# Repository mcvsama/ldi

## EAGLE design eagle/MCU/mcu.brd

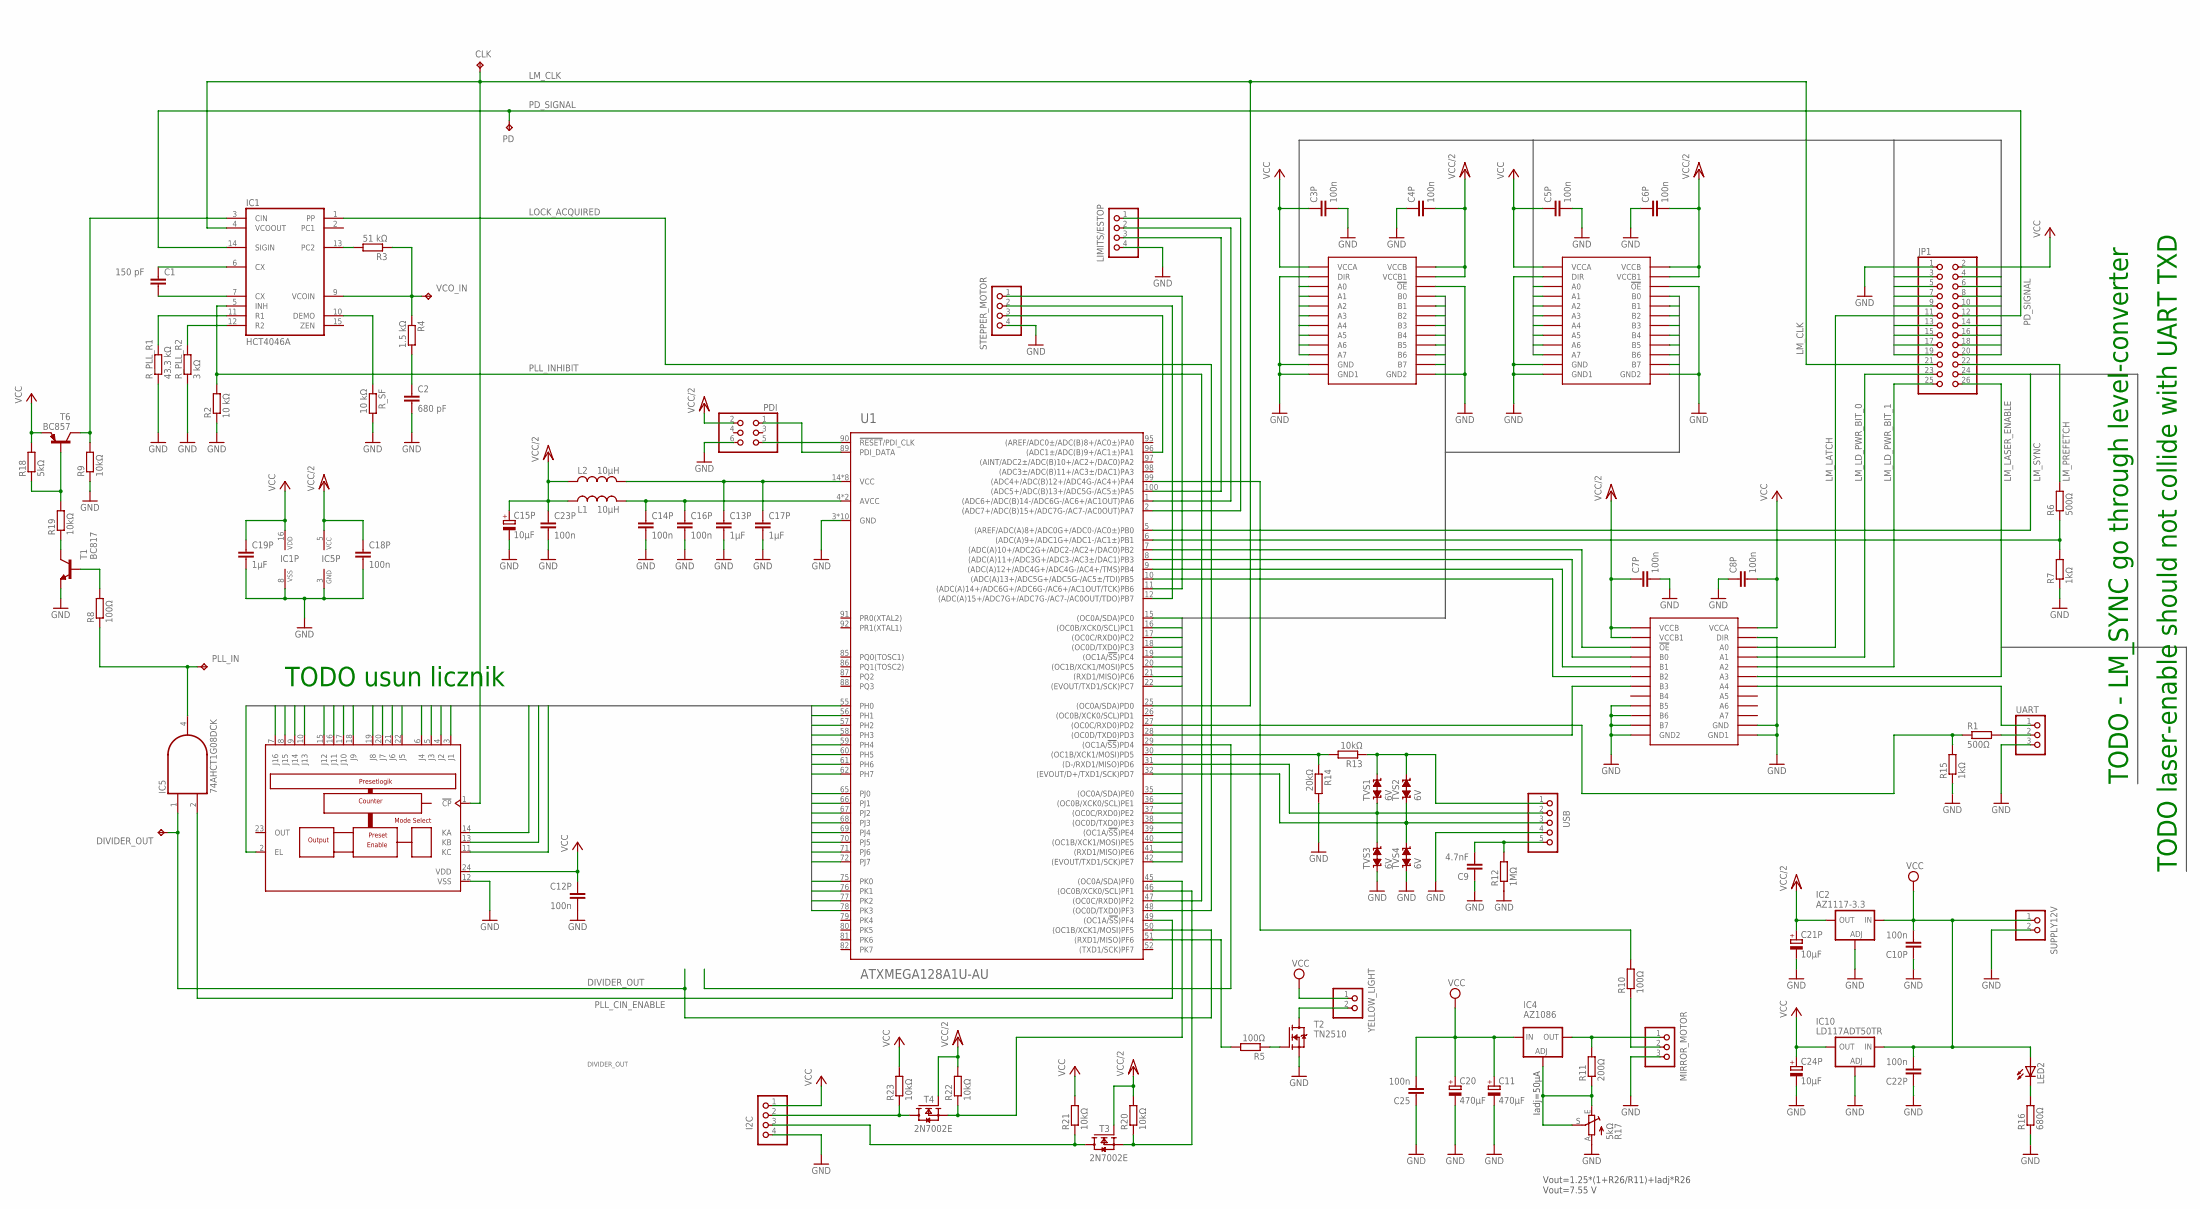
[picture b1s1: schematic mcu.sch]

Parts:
C1: 150 pF; C1206
C2: 680 pF; C1206
C3P, C4P, C5P, C6P, C7P, C8P: 100n; C0603
C9: 4.7nF; C1206
C10P, C12P, C14P, C16P, C18P, C22P, C23P, C25: 100n; C1206
C11, C20: 470µF; 153CLV-0807
C13P, C17P, C19P: 1µF; C1206
C15P, C21P, C24P: 10µF; A/3216-18R
CLK: TPB1,27; B1,27
DIVIDER_OUT: TPB1,27; B1,27
I2C: PINHD-1X4; 1X04
IC1: HCT4046A; SO16
IC2: AZ1117-3.3; DPACK
IC3: 4059D; SO24W
IC4: AZ1086; D2PACK
IC5: 74AHCT1G08DCK; SC70-5
IC7, IC8, IC9: 74LVX4245TSSOP24W; TSSOP-24-W
IC10: LD117ADT50TR; DPACK
JP1: PINHD-2X13; 2X13
L1, L2: 10µH; L1812
LED2: LEDCHIPLED_0805; CHIPLED_0805
LIMITS/ESTOP: PINHD-1X4; 1X04
MIRROR_MOTOR: PINHD-1X3; 1X03
PD: TPB1,27; B1,27
PDI: PINHD-2X3; 2X03
PLL_IN: TPB1,27; B1,27
R1, R6: 500Ω; R0603
R2: 10 kΩ; R0603
R3: 51 kΩ; R0603
R4: 1.5 kΩ; R0603
R5, R8, R10: 100Ω; R0603
R7, R15: 1kΩ; R0603
R9, R13, R19, R20, R21, R22, R23: 10kΩ; R0603
R11: 200Ω; R1206
R12: 1MΩ; R0603
R14: 20kΩ; R0603
R16: 680Ω; R0603
R17: 5kΩ; B64Y
R18: 5kΩ; R0603
R_PLL_R1: 43.3 kΩ; R0603
R_PLL_R2: 3 kΩ; R0603
R_SF: 10 kΩ; R0603
STEPPER_MOTOR: PINHD-1X4; 1X04
SUPPLY12V: PINHD-1X2; 1X02
T1: BC817; SOT23-BEC
T2: TN2510; SOT89
T3, T4: 2N7002E; SOT23
T6: BC857; SOT23-BEC
TVS1, TVS2, TVS3, TVS4: 6V; TVS0805
U1: ATXMEGA128A1U-AU; TQFP-100A-100
UART: PINHD-1X3; 1X03
USB: PINHD-1X5; 1X05
VCO_IN: TPB1,27; B1,27
YELLOW_LIGHT: PINHD-1X2; 1X02

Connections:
CTR0_KA: IC3.14 (KA), U1.75 (PK0)
CTR0_KB: IC3.13 (KB), U1.76 (PK1)
CTR0_KC: IC3.11 (KC), U1.77 (PK2)
CTR0_LE: IC3.2 (EL), U1.78 (PK3)
CTR0_PROG0: IC3.3 (J1), U1.55 (PH0)
CTR0_PROG1: IC3.4 (J2), U1.56 (PH1)
CTR0_PROG2: IC3.5 (J3), U1.57 (PH2)
CTR0_PROG3: IC3.6 (J4), U1.58 (PH3)
CTR0_PROG4: IC3.22 (J5), U1.59 (PH4)
CTR0_PROG5: IC3.21 (J6), U1.60 (PH5)
CTR0_PROG6: IC3.20 (J7), U1.61 (PH6)
CTR0_PROG7: IC3.19 (J8), U1.62 (PH7)
CTR0_PROG8: IC3.18 (J9), U1.65 (PJ0)
CTR0_PROG9: IC3.17 (J10), U1.66 (PJ1)
CTR0_PROG10: IC3.16 (J11), U1.67 (PJ2)
CTR0_PROG11: IC3.15 (J12), U1.68 (PJ3)
CTR0_PROG12: IC3.10 (J13), U1.69 (PJ4)
CTR0_PROG13: IC3.9 (J14), U1.70 (PJ5)
CTR0_PROG14: IC3.8 (J15), U1.71 (PJ6)
CTR0_PROG15: IC3.7 (J16), U1.72 (PJ7)
DIVIDER_OUT: DIVIDER_OUT.TP, IC5.1 (I0), U1.50 ((OC1B/XCK1/MOSI)PF5)
GND: C2.2, C3P.2, C4P.1, C5P.2, C6P.1, C7P.2, C8P.1, C9.1, C10P.1, C11.-, C12P.1, C13P.2, C14P.2, C15P.-, C16P.2, C17P.2, C18P.2, C19P.2, C20.-, C21P.-, C22P.1, C23P.2, C24P.-, C25.1, I2C.4, IC1.8 (VSS), IC2.1 (ADJ), IC3.12 (VSS), IC5.3 (GND), IC7.2 (DIR), IC7.11 (GND), IC7.12 (GND1), IC7.13 (GND2), IC7.22 (!OE), IC8.2 (DIR), IC8.11 (GND), IC8.12 (GND1), IC8.13 (GND2), IC8.22 (!OE), IC9.2 (DIR), IC9.11 (GND), IC9.12 (GND1), IC9.13 (GND2), IC9.14 (B7), IC9.15 (B6), IC9.16 (B5), IC10.1 (ADJ), JP1.1, LIMITS/ESTOP.4, MIRROR_MOTOR.3, PDI.6, R2.1, R7.1, R9.1, R12.1, R14.2, R15.1, R16.1, R17.A, R_PLL_R1.1, R_PLL_R2.1, R_SF.2, STEPPER_MOTOR.4, SUPPLY12V.2, T1.E, T2.3 (S), TVS3.1, TVS4.1, U1.3 (GND), U1.13 (GND), U1.23 (GND), U1.33 (GND), U1.43 (GND), U1.53 (GND), U1.63 (GND), U1.73 (GND), U1.84 (GND), U1.93 (GND), UART.3, USB.4
I2C_SDA_3V2: R20.1, T3.2 (S), U1.46 ((OC0B/XCK0/SCL)PF1)
I2C_SDA_3V4: R22.1, T4.2 (S), U1.45 ((OC0A/SDA)PF0)
I2C_SDA_5V2: I2C.3, R21.1, T3.3 (D)
I2C_SDA_5V3: I2C.2, R23.1, T4.3 (D)
LM_CLK: CLK.TP, IC1.4 (VCOOUT), IC3.1 (!CP), JP1.21, U1.25 ((OC0A/SDA)PD0)
LM_DATA_3V3_0: IC7.21 (B0), U1.35 ((OC0A/SDA)PE0)
LM_DATA_3V3_1: IC7.20 (B1), U1.36 ((OC0B/XCK0/SCL)PE1)
LM_DATA_3V3_2: IC7.19 (B2), U1.37 ((OC0C/RXD0)PE2)
LM_DATA_3V3_3: IC7.18 (B3), U1.38 ((OC0D/TXD0)PE3)
LM_DATA_3V3_4: IC7.17 (B4), U1.39 ((OC1A/!SS!)PE4)
LM_DATA_3V3_5: IC7.16 (B5), U1.40 ((OC1B/XCK1/MOSI)PE5)
LM_DATA_3V3_6: IC7.15 (B6), U1.41 ((RXD1/MISO)PE6)
LM_DATA_3V3_7: IC7.14 (B7), U1.42 ((EVOUT/TXD1/SCK)PE7)
LM_DATA_3V3_8: IC8.21 (B0), U1.15 ((OC0A/SDA)PC0)
LM_DATA_3V3_9: IC8.20 (B1), U1.16 ((OC0B/XCK0/SCL)PC1)
LM_DATA_3V3_10: IC8.19 (B2), U1.17 ((OC0C/RXD0)PC2)
LM_DATA_3V3_11: IC8.18 (B3), U1.18 ((OC0D/TXD0)PC3)
LM_DATA_3V3_12: IC8.17 (B4), U1.19 ((OC1A/!SS!)PC4)
LM_DATA_3V3_13: IC8.16 (B5), U1.20 ((OC1B/XCK1/MOSI)PC5)
LM_DATA_3V3_14: IC8.15 (B6), U1.21 ((RXD1/MISO)PC6)
LM_DATA_3V3_15: IC8.14 (B7), U1.22 ((EVOUT/TXD1/SCK)PC7)
LM_DATA_5V0: IC7.10 (A7), JP1.3
LM_DATA_5V1: IC7.9 (A6), JP1.4
LM_DATA_5V2: IC7.8 (A5), JP1.5
LM_DATA_5V3: IC7.7 (A4), JP1.6
LM_DATA_5V4: IC7.6 (A3), JP1.7
LM_DATA_5V5: IC7.5 (A2), JP1.8
LM_DATA_5V6: IC7.4 (A1), JP1.9
LM_DATA_5V7: IC7.3 (A0), JP1.10
LM_DATA_5V8: IC8.10 (A7), JP1.13
LM_DATA_5V9: IC8.9 (A6), JP1.14
LM_DATA_5V10: IC8.8 (A5), JP1.15
LM_DATA_5V11: IC8.7 (A4), JP1.16
LM_DATA_5V12: IC8.6 (A3), JP1.17
LM_DATA_5V13: IC8.5 (A2), JP1.18
LM_DATA_5V14: IC8.4 (A1), JP1.19
LM_DATA_5V15: IC8.3 (A0), JP1.20
LM_LASER_ENABLE: IC9.6 (A3), JP1.26
LM_LATCH: IC9.3 (A0), JP1.11
LM_LD_PWR_BIT_0: IC9.4 (A1), JP1.23
LM_LD_PWR_BIT_1: IC9.5 (A2), JP1.25
LM_PREFETCH: JP1.22, R6.2
LM_SYNC: JP1.24
LOCK_ACQUIRED: IC1.1 (PP), U1.48 ((OC0D/TXD0)PF3)
unnamed: R6.1, R7.2, U1.6 ((ADC(A)9+/ADC1G+/ADC1-/AC1±)PB1)
unnamed: R18.1, R19.2, T6.B
unnamed: LIMITS/ESTOP.3, U1.100 ((ADC5+/ADC(B)13+/ADC5G-/AC5±)PA5)
unnamed: R5.2, U1.51 ((RXD1/MISO)PF6)
unnamed: PDI.1, U1.89 (PDI_DATA)
unnamed: C1.1, IC1.6 (CX)
unnamed: IC9.22 (!OE), U1.7 ((ADC(A)10+/ADC2G+/ADC2-/AC2+/DAC0)PB2)
unnamed: C1.2, IC1.7 (CX)
unnamed: IC1.13 (PC2), R3.2
unnamed: IC1.9 (VCOIN), R3.1, R4.1, VCO_IN.TP
unnamed: C2.1, R4.2
unnamed: IC1.10 (DEMO), R_SF.1
unnamed: IC1.11 (R1), R_PLL_R1.2
unnamed: IC1.12 (R2), R_PLL_R2.2
unnamed: IC9.21 (B0), U1.8 ((ADC(A)11+/ADC3G+/ADC3-/AC3±/DAC1)PB3)
unnamed: IC9.20 (B1), U1.9 ((ADC(A)12+/ADC4G+/ADC4G-/AC4+/TMS)PB4)
unnamed: IC9.19 (B2), U1.10 ((ADC(A)13+/ADC5G+/ADC5G-/AC5±/TDI)PB5)
unnamed: IC4.1 (ADJ), R11.1, R17.E, R17.S
unnamed: IC4.2 (OUT), MIRROR_MOTOR.1, R11.2
unnamed: R10.2, U1.99 ((ADC4+/ADC(B)12+/ADC4G-/AC4+)PA4)
unnamed: T2.2 (D), T2.2@1 (D), YELLOW_LIGHT.2
unnamed: R5.1, T2.1 (G)
unnamed: PDI.5, U1.90 (!RESET!/PDI_CLK)
unnamed: TVS1.1, TVS3.2, U1.31 ((D-/RXD1/MISO)PD6), USB.2
unnamed: TVS2.1, TVS4.2, U1.32 ((EVOUT/D+/TXD1/SCK)PD7), USB.3
unnamed: R1.1, R15.2, U1.27 ((OC0C/RXD0)PD2)
unnamed: MIRROR_MOTOR.2, R10.1
unnamed: IC9.18 (B3), U1.28 ((OC0D/TXD0)PD3)
unnamed: R13.1, TVS1.2, TVS2.2, USB.1
unnamed: C9.2, R12.2, USB.5
unnamed: R13.2, R14.1, U1.30 ((OC1B/XCK1/MOSI)PD5)
unnamed: STEPPER_MOTOR.3, U1.96 ((ADC1±/ADC(B)9+/AC1±)PA1)
unnamed: LIMITS/ESTOP.2, U1.1 ((ADC6+/ADC(B)14-/ADC6G-/AC6+/AC1OUT)PA6)
unnamed: LIMITS/ESTOP.1, U1.2 ((ADC7+/ADC(B)15+/ADC7G-/AC7-/AC0OUT)PA7)
unnamed: STEPPER_MOTOR.1, U1.11 ((ADC(A)14+/ADC6G+/ADC6G-/AC6+/AC1OUT/TC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)
unnamed: STEPPER_MOTOR.2, U1.12 ((ADC(A)15+/ADC7G+/ADC7G-/AC7-/AC0OUT/TD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)
unnamed: LED2.C, R16.2
unnamed: IC9.7 (A4), UART.1
unnamed: R1.2, UART.2
unnamed: R8.2, T1.B
unnamed: R19.1, T1.C
unnamed: C13P.1, C17P.1, L2.1, U1.14 (VCC), U1.24 (VCC), U1.34 (VCC), U1.44 (VCC), U1.54 (VCC), U1.64 (VCC), U1.74 (VCC), U1.83 (VCC)
unnamed: C14P.1, C16P.1, L1.1, U1.4 (AVCC), U1.94 (AVCC)
PD4: U1.29 ((OC1A/!SS!)PD4)
PD_SIGNAL: IC1.14 (SIGIN), JP1.12, PD.TP
PLL_CIN_ENABLE: IC5.2 (I1), U1.49 ((OC1A/!SS!)PF4)
PLL_INHIBIT: IC1.5 (INH), R2.2, U1.47 ((OC0C/RXD0)PF2)
PLL_IN_3V3: IC5.4 (O), PLL_IN.TP, R8.1
PLL_IN_5V: IC1.3 (CIN), R9.2, T6.C
VCC/3.3V: C4P.2, C6P.2, C7P.1, C15P.+, C18P.1, C21P.+, C23P.1, IC2.4 (OUT), IC5.5 (VCC), IC7.23 (VCCB1), IC7.24 (VCCB), IC8.23 (VCCB1), IC8.24 (VCCB), IC9.23 (VCCB1), IC9.24 (VCCB), L1.2, L2.2, PDI.2, R20.2, R22.2, T3.1 (G), T4.1 (G)
VCC/5V: C3P.1, C5P.1, C8P.2, C12P.2, C19P.1, C24P.+, I2C.1, IC1.16 (VDD), IC3.24 (VDD), IC7.1 (VCCA), IC8.1 (VCCA), IC9.1 (VCCA), IC10.4 (OUT), JP1.2, R18.2, R21.2, R23.2, T6.E
VCC/12V: C10P.2, C11.+, C20.+, C22P.2, C25.2, IC2.3 (IN), IC4.3 (IN), IC10.3 (IN), LED2.A, SUPPLY12V.1, YELLOW_LIGHT.1

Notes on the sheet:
Vout=1.25*(1+R26/R11)+Iadj*R26 Vout=7.55 V
Iadj=50µA
TODO - LM_SYNC go through level-converter
TODO laser-enable should not collide with UART TXD
TODO usun licznik

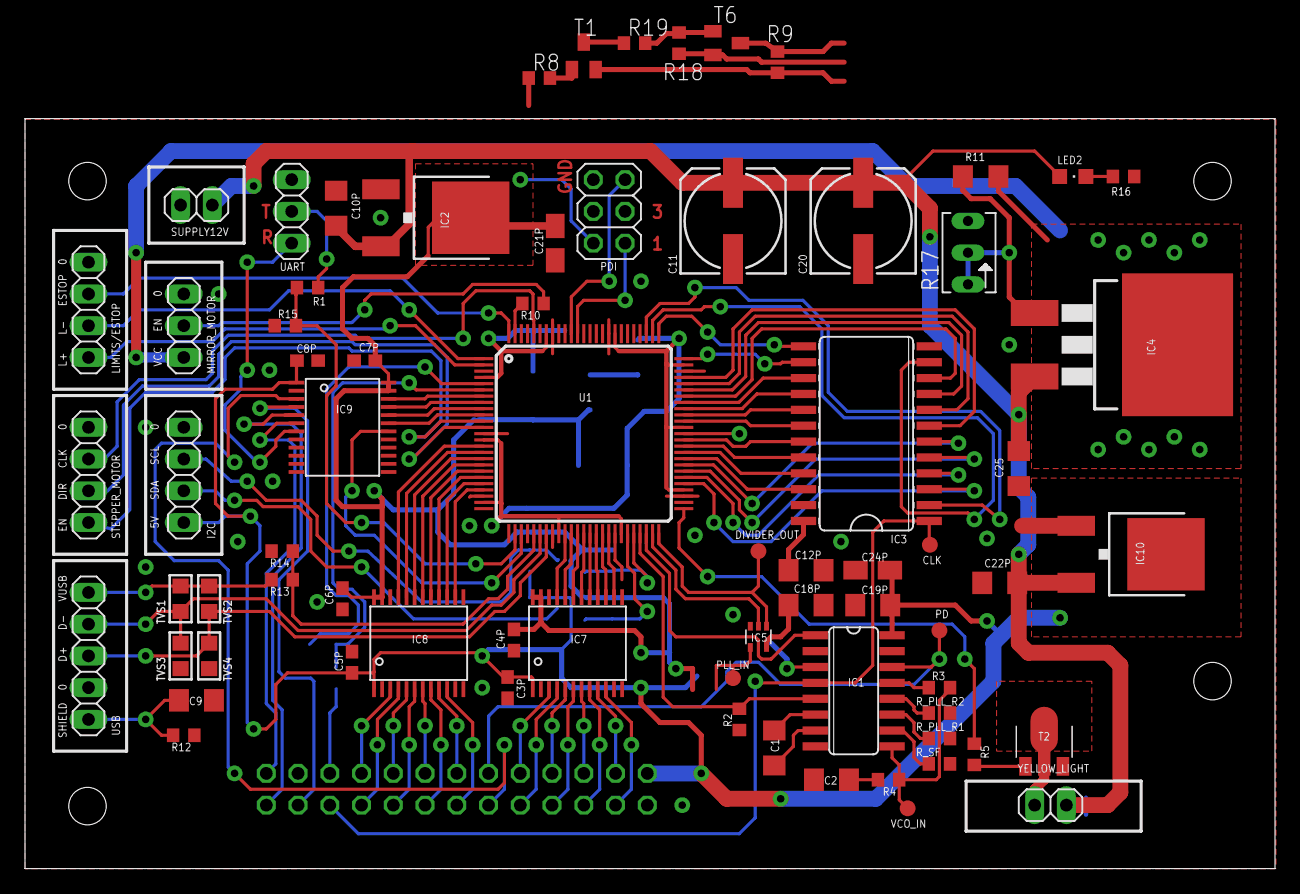
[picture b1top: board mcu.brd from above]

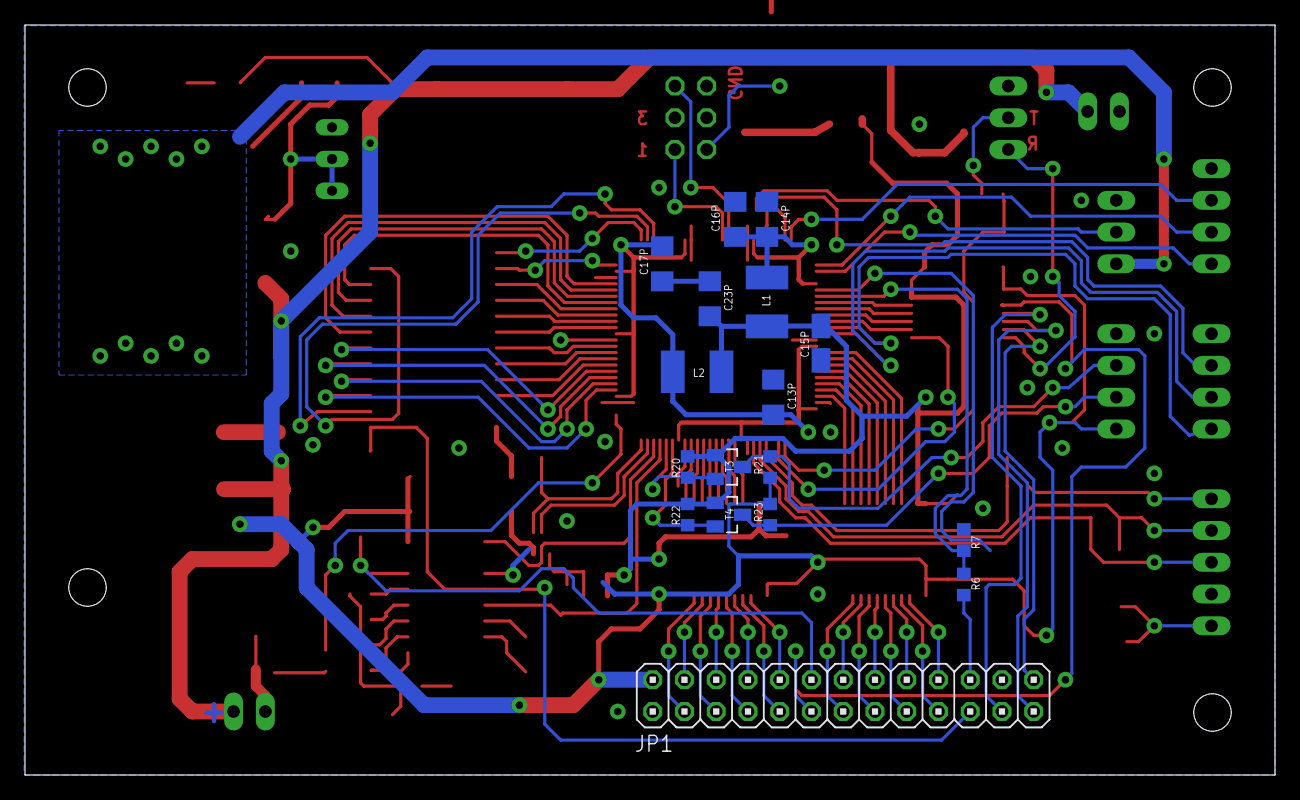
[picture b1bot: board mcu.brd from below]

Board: 2 copper layers, 100.0 x 60.0 mm, 88 parts (17 on the bottom side), 116 nets.

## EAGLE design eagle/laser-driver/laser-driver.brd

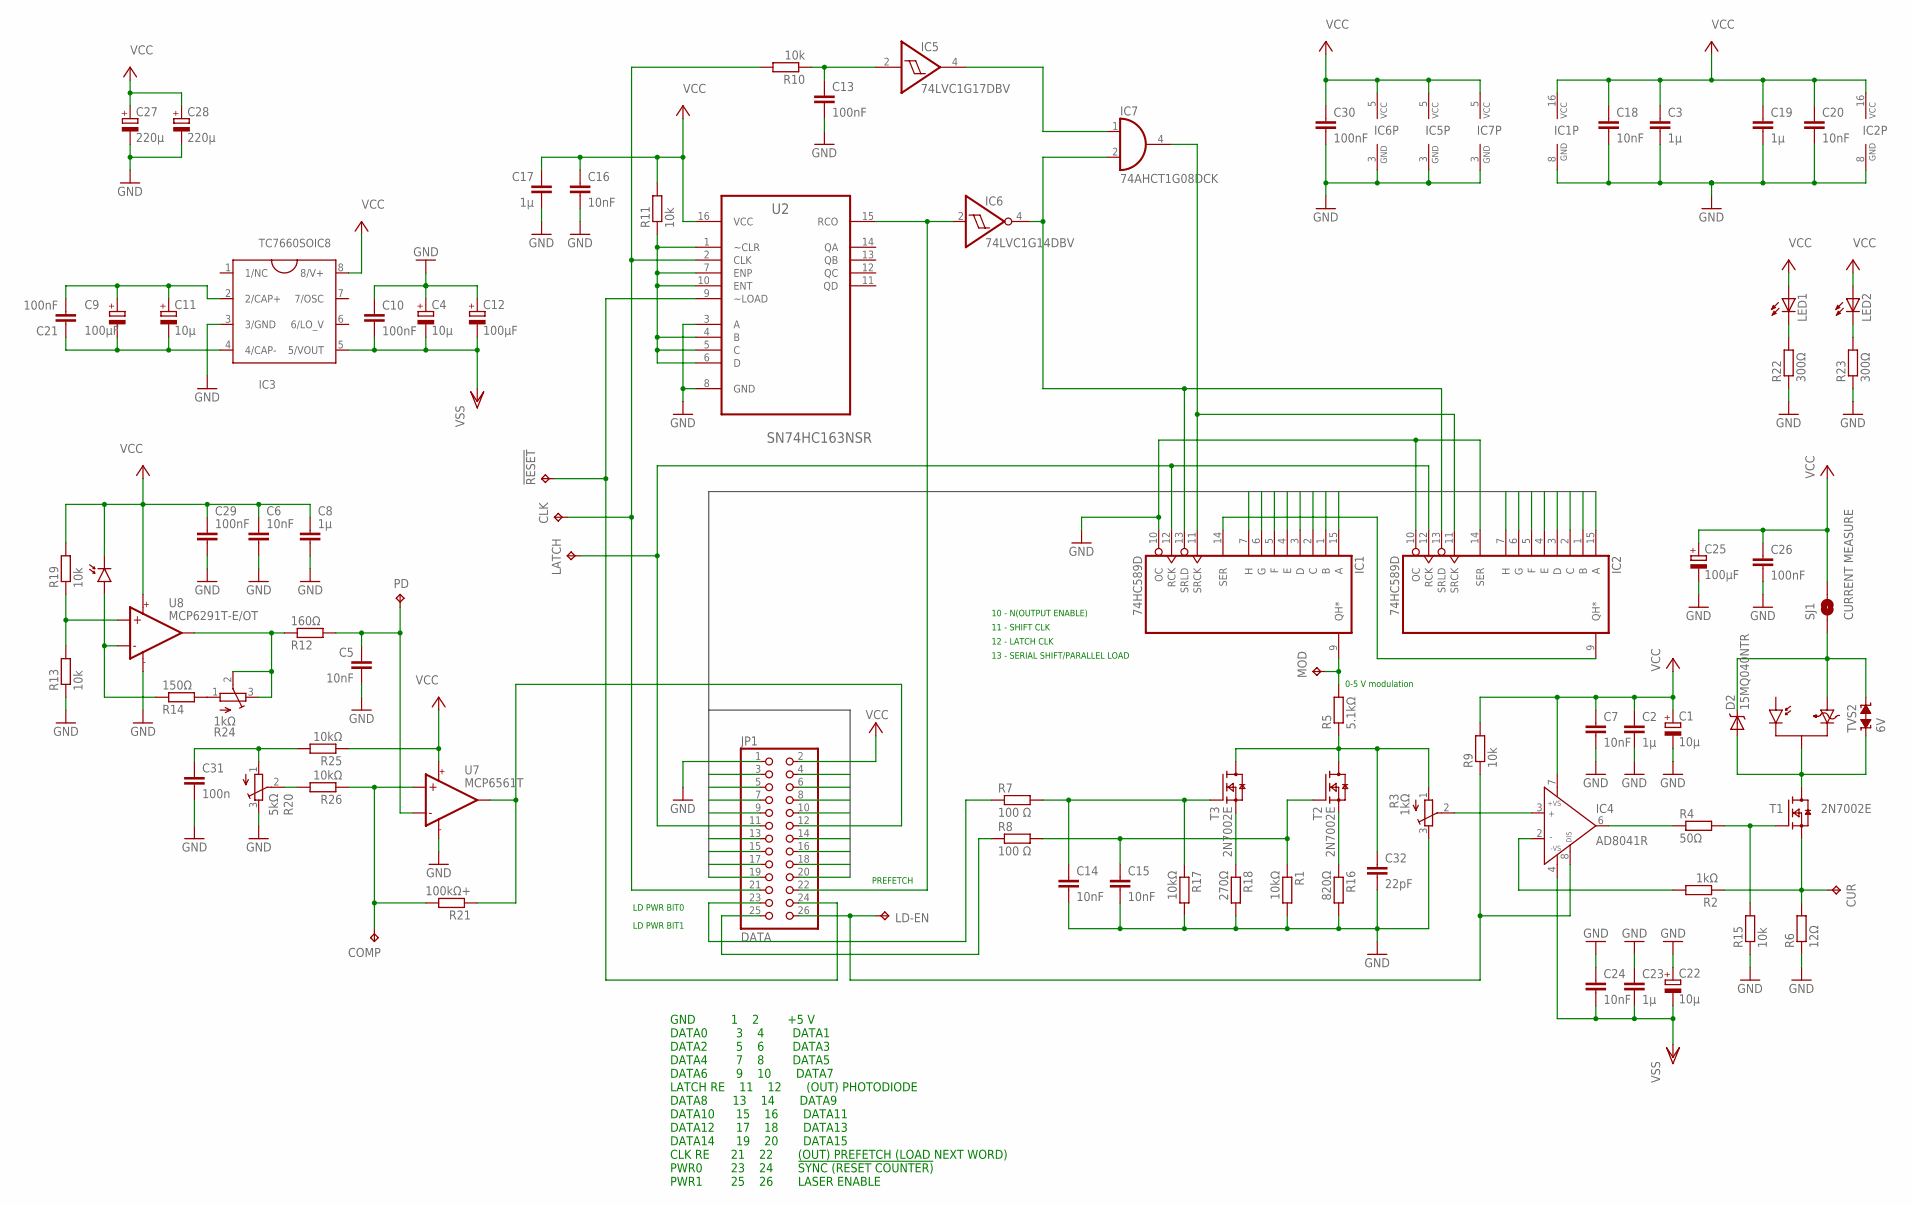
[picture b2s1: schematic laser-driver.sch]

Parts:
!RESET: TPB1,27; B1,27
C1, C4, C11, C22: 10µ; A/3216-18R
C2, C3, C8, C17, C19, C23: 1µ; C1206
C5: 10nF; C0603
C6, C7, C14, C15, C16, C18, C20, C24: 10nF; C1206
C9, C12, C25: 100µF; D/7343-31R
C10, C21: 100nF; C1206
C13, C26, C29, C30: 100nF; C0603
C27, C28: 220µ; 153CLV-0605
C31: 100n; C0603
C32: 22pF; C0603
CLK: TPB1,27; B1,27
COMP: TPB1,27; B1,27
CUR: TPB1,27; B1,27
D2: 15MQ040NTR; SMA-DIODE
D3: VTB8441BH
IC1, IC2: 74HC589D; SO16
IC3: TC7660SOIC8; SOIC8
IC4: AD8041R; SO8
IC5: 74LVC1G17DBV; SOT23-5
IC6: 74LVC1G14DBV; SOT23-5
IC7: 74AHCT1G08DCK; SC70-5
JP1: DATA; 2X13
LATCH: TPB1,27; B1,27
LD-EN: TPB1,27; B1,27
LED1, LED2: LEDCHIPLED_0805; CHIPLED_0805
MOD: TPB1,27; B1,27
PD: TPB1,27; B1,27
R1, R17, R25, R26: 10kΩ; R0603
R2: 1kΩ; R0603
R3: 1kΩ; SM-42/43B
R4: 50Ω; R0603
R5: 5.1kΩ; R0603
R6: 12Ω; R0603
R7, R8: 100 Ω; R0603
R9, R10, R11, R13, R15, R19: 10k; R0603
R12: 160Ω; R0603
R14: 150Ω; R0603
R16: 820Ω; R0603
R18: 270Ω; R0603
R20: 5kΩ; SM-42/43B
R21: 100kΩ+; R0603
R22, R23: 300Ω; R0603
R24: 1kΩ; 3223G
SJ1: CURRENT MEASURE; SJ_2S-NO
T1, T2, T3: 2N7002E; SOT23
TVS2: 6V; TVS0805
U2: SN74HC163NSR; SOIC127P780X200-16N
U7: MCP6561T; SOT23-5
U8: MCP6291T-E/OT; SOT23-5
U$1: LASER-LED-COMMON-CATHODE; TO-18

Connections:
0…5: IC1.9 (QH*), MOD.TP, R5.2
GND: C1.-, C2.2, C3.2, C4.+, C5.2, C6.2, C7.2, C8.2, C10.1, C12.+, C13.2, C14.2, C15.2, C16.2, C17.2, C18.2, C19.2, C20.2, C22.+, C23.1, C24.1, C25.-, C26.2, C27.-, C28.-, C29.2, C30.2, C31.2, C32.2, IC1.8 (GND), IC1.10 (OC), IC2.8 (GND), IC2.10 (OC), IC2.14 (SER), IC3.3 (3/GND), IC5.3 (GND), IC6.3 (GND), IC7.3 (GND), JP1.1, R1.2, R3.3 (E), R6.1, R13.1, R15.1, R16.2, R17.2, R18.2, R20.3 (E), R22.1, R23.1, U2.3 (A), U2.8 (GND), U7.2 (VCC-), U8.2 (VCC-)
IN0: IC2.15 (A), JP1.3
IN1: IC2.1 (B), JP1.4
IN2: IC2.2 (C), JP1.5
IN3: IC2.3 (D), JP1.6
IN4: IC2.4 (E), JP1.7
IN5: IC2.5 (F), JP1.8
IN6: IC2.6 (G), JP1.9
IN7: IC2.7 (H), JP1.10
IN8: IC1.15 (A), JP1.13
IN9: IC1.1 (B), JP1.14
IN10: IC1.2 (C), JP1.15
IN11: IC1.3 (D), JP1.16
IN12: IC1.4 (E), JP1.17
IN13: IC1.5 (F), JP1.18
IN14: IC1.6 (G), JP1.19
IN15: IC1.7 (H), JP1.20
unnamed: IC4.8 (DISABLE), JP1.26, LD-EN.TP, R9.1
unnamed: C32.1, R3.1 (A), R5.1, T2.3 (D), T3.3 (D)
unnamed: IC4.6 (OUT), R4.1
unnamed: R4.2, R15.2, T1.1 (G)
unnamed: D2.A, T1.3 (D), TVS2.1, U$1.3
unnamed: CUR.TP, R2.1, R6.2, T1.2 (S)
unnamed: JP1.23, R7.1
unnamed: IC4.3 (IN+), R3.2 (S)
unnamed: C14.1, R7.2, R17.1, T3.1 (G)
unnamed: JP1.25, R8.1
unnamed: !RESET.TP, JP1.24, U2.9 (~LOAD)
unnamed: JP1.12, R21.1, U7.1 (OUT)
unnamed: C15.1, R1.1, R8.2, T2.1 (G)
unnamed: IC1.14 (SER), IC2.9 (QH*)
unnamed: C9.+, C11.+, C21.2, IC3.2 (2/CAP+)
unnamed: IC1.11 (SRCK), IC2.11 (SRCK), IC7.4 (O)
unnamed: IC1.13 (SRLD), IC2.13 (SRLD), IC6.4 (O), IC7.2 (I1)
unnamed: R11.1, U2.1 (~CLR), U2.4 (B), U2.5 (C), U2.6 (D), U2.7 (ENP), U2.10 (ENT)
unnamed: COMP.TP, R21.2, R26.1, U7.3 (IN+)
unnamed: IC6.2 (I), JP1.22, U2.15 (RCO)
unnamed: D3.A, R14.1, U8.4 (IN-)
unnamed: CLK.TP, JP1.21, R10.2, U2.2 (CLK)
unnamed: R12.1, R24.2 (S), R24.3 (E), U8.1 (OUT)
unnamed: C13.1, IC5.2 (I), R10.1
unnamed: C9.-, C11.-, C21.1, IC3.4 (4/CAP-)
unnamed: IC1.12 (RCK), IC2.12 (RCK), JP1.11, LATCH.TP
unnamed: IC5.4 (O), IC7.1 (I0)
unnamed: R16.1, T2.2 (S)
unnamed: R18.1, T3.2 (S)
unnamed: R13.2, R19.1, U8.3 (IN+)
unnamed: D2.C, SJ1.1, TVS2.2, U$1.1
unnamed: C5.1, PD.TP, R12.2, U7.4 (IN-)
unnamed: LED1.C, R22.2
unnamed: LED2.C, R23.2
unnamed: IC4.2 (IN-), R2.2
unnamed: R14.2, R24.1 (A)
unnamed: C31.1, R20.1 (A), R25.2
unnamed: R20.2 (S), R26.2
VCC: C1.+, C2.1, C3.1, C6.1, C7.1, C8.1, C16.1, C17.1, C18.1, C19.1, C20.1, C25.+, C26.1, C27.+, C28.+, C29.1, C30.1, D3.K, IC1.16 (VCC), IC2.16 (VCC), IC3.8 (8/V+), IC4.7 (+VS), IC5.5 (VCC), IC6.5 (VCC), IC7.5 (VCC), JP1.2, LED1.A, LED2.A, R9.2, R11.2, R19.2, R25.1, SJ1.2, U2.16 (VCC), U7.5 (VCC+), U8.5 (VCC+)
VSS: C4.-, C10.2, C12.-, C22.-, C23.2, C24.2, IC3.5 (5/VOUT), IC4.4 (-VS)

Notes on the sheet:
0-5 V modulation
LD PWR BIT0
LD PWR BIT1
10 - N(OUTPUT ENABLE) 11 - SHIFT CLK 12 - LATCH CLK 13 - SERIAL SHIFT/PARALLEL LOAD
PREFETCH
GND 1 2 +5 V DATA0 3 4 DATA1 DATA2 5 6 DATA3 DATA4 7 8 DATA5 DATA6 9 10 DATA7 LATCH RE 11 12 (OUT) PHOTODIODE DATA8 13 14 DATA9 DATA10 15 16 DATA11 DATA12 17 18 DATA13 DATA14 19 20 DATA15 CLK RE 21 22 (OUT) PREFETCH (LOAD NEXT WORD) PWR0 23 24 !SYNC (RESET COUNTER) PWR1 25 26 LASER ENABLE

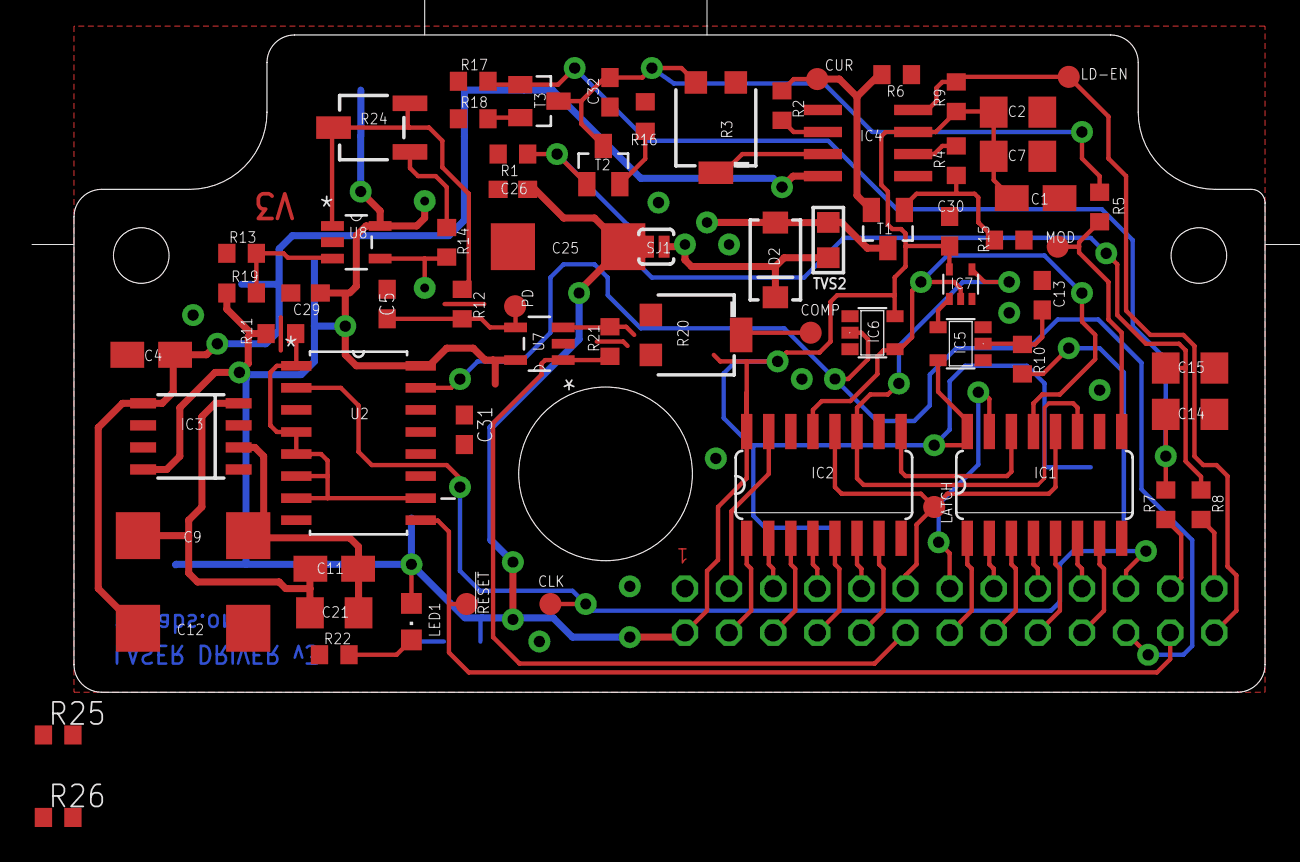
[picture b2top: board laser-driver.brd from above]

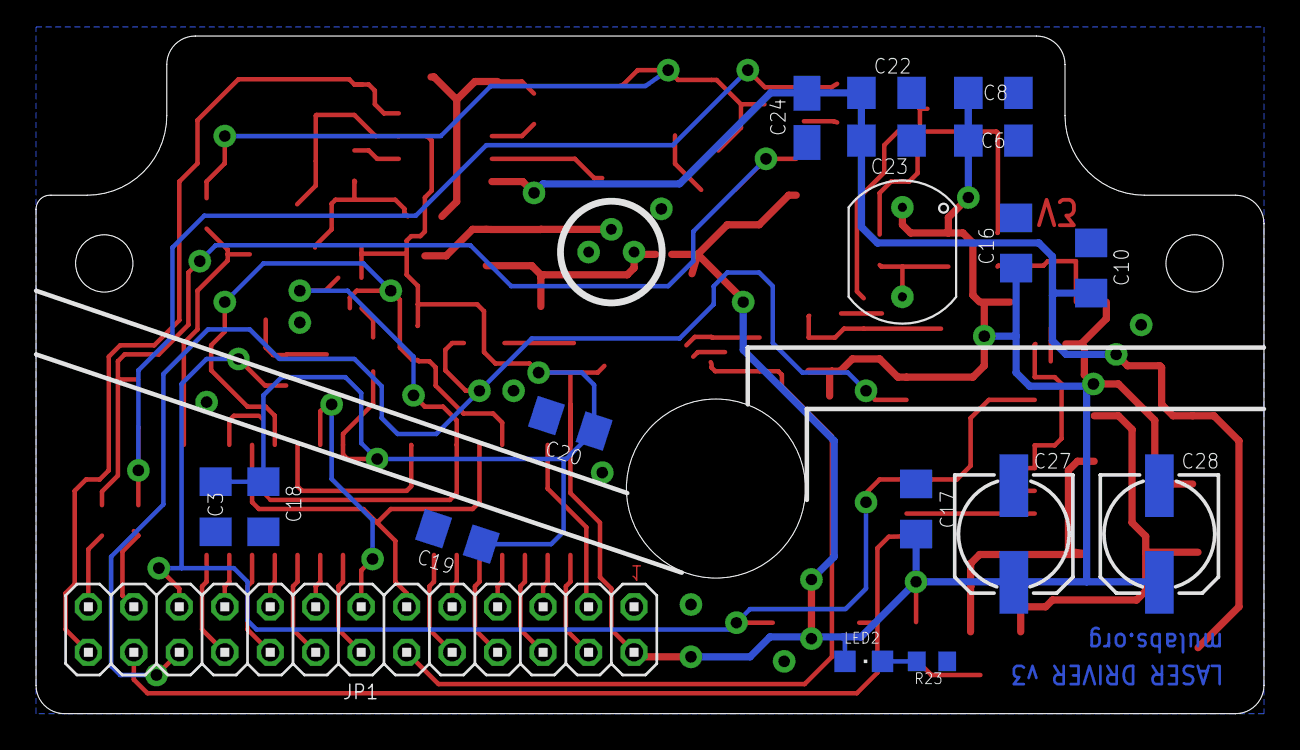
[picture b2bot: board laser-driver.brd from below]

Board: 2 copper layers, 68.6 x 37.8 mm, 87 parts (19 on the bottom side), 58 nets.

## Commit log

2014-12-22 Import laser driver module.
2016-08-14 Update PCBs, schematics, processed jobs, etc.
2016-08-14 Firmware update
2017-04-23 PLL acquires lock
2017-04-28 Next version
2017-11-19 Rename firmware file to firmware.cc

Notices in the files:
parts and their libraries:
supressor: Copyright (C) 2009, Bob Starr
SparkFun: Licensing: CC v3.0 Share-Alike You are welcome to use this library for commercial purposes.
